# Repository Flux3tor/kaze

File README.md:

# kaze.

kaze is a custom 65%-style mechanical keyboard powered by the Raspberry Pi Pico (RP2040). It features a custom-designed PCB, a compact 3D-printed case, and RMK firmware.

---

## Why did I make it?

I wanted to build my own keyboard instead of buying one off the shelf. kaze is my take on a compact, silent mechanical keyboard, designed around the layout and features I actually want.

---

## Project Images

### Schematic

### PCB

### PCB Render

### Case Render

---

Features:
- 68-key custom layout
- Raspberry Pi Pico (RP2040) controller
- Custom KiCad PCB and schematic
- Individual diodes for the switch matrix
- Custom case design
- RMK firmware written in Rust
- Base layer and Fn layer
- Dedicated arrow keys
- Brightness and volume controls in the keymap

---

## Firmware

Kaze. uses [RMK](https://github.com/HaoboGu/rmk), a Rust-based keyboard firmware.

The firmware configuration is in [`Firmware/keyboard.toml`](Firmware/keyboard.toml), and the configurator definition is in [`Firmware/vial.json`](Firmware/vial.json).

---

## BOM

| Name | Purpose | Quantity | Unit Cost (USD) | Total Cost (USD) | Distributor |
|---|---|---:|---:|---:|---|
| [Akko V3 Fairy Pro Switches (Pack of 45)](https://stackskb.com/store/akko-fairy-pro-switch-pack-of-45/) | Mechanical switches | 2 | $16.00 | $32.00 | StacksKB |
| [Lakes Mountains Premium Cherry PBT Extended Keycaps](https://curiositycaps.in/products/lakes-mountains-premium-cherry-pbt-extended-keycaps) | Keycaps | 1 | $29.00 | $29.00 | Curiosity Caps |
| [Durock Clear Screw-In Stabilizers V2](https://stackskb.com/store/durock-clear-screw-in-stabilizers-v2/?attribute_combination=4%2B1+Set&attribute_spacebar-size=6.25U) | Stabilizers | 1 | $17.00 | $17.00 | StacksKB |
| [1N4148 Through-Hole Diodes (Pack of 10)](https://stackskb.com/store/1n4148-through-hole-diode/) | Matrix diodes | 7 | $0.20 | $2 | StacksKB |
| [LuatOS USB-C Raspberry Pi Pico Development Board](https://makerbazar.in/products/luatos-usb-c-raspberry-pi-pico-development-board-based-on-rp2040-microcontroller) | Main controller | 1 | $5.00 | $5.00 | MakerBazar |
| [Portronics Type-C to Type-C Cable](https://www.amazon.in/dp/B09Q8XMFHB?ref_=cm_sw_r_cp_ud_dp_9F8YCTNXZB2SQ3WDDXEK_1) | USB connection | 1 | $2.00 | $2.00 | Amazon |
| [PLA Filament](https://india.numakers.com/products/pla-filament) | 3D-printed case | 1 | Already owned | $0.00 | Numakers |
| PCB | Keyboard circuit board | 5 | 25 | 25 | Offline/Local Fabricator |
| M2 Screws | Case mounting | 6 | Already owned | $0.00 | Already owned |
| M2 Brass Inserts | Case mounting inserts | 6 | Already owned | $0.00 | Already owned |

## Total Pricing
The total price comes out to be **₹10,600 ($112), including shipping, and taxes.**

---

## Project Files

- `CAD/` - case and assembly CAD files
- `Firmware/` - firmware configuration and UF2 file
- `Images/` - project renders and schematic/PCB images
- `PCB/` - KiCad schematic, PCB, and production files

---

Made with <3 by [Flux3tor](https://github.com/Flux3tor)

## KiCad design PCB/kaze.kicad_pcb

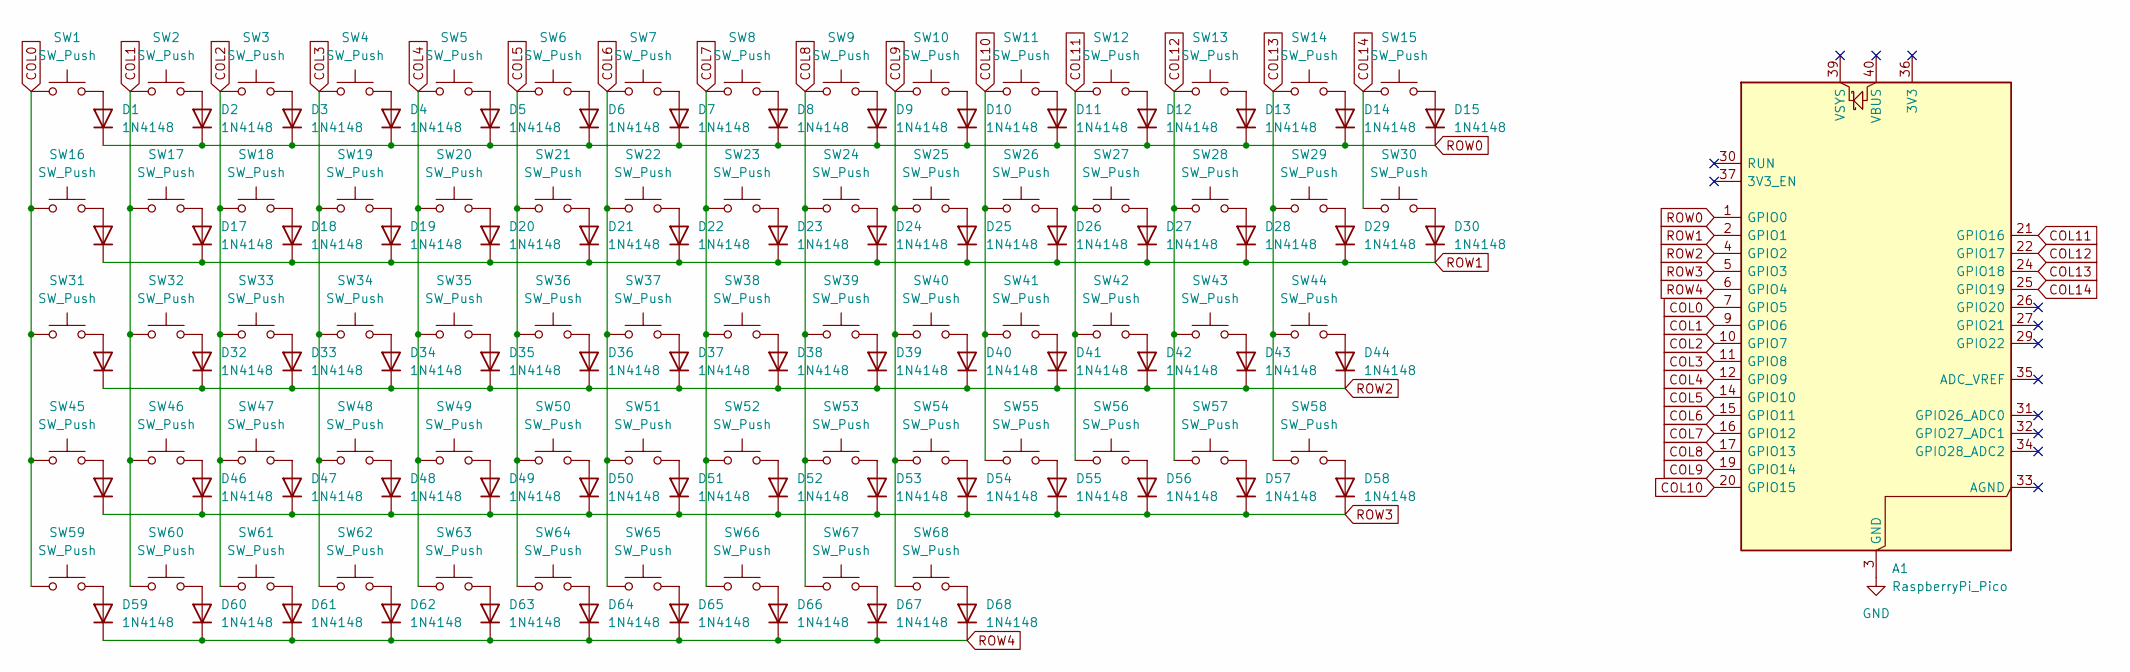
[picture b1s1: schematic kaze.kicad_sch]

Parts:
A1: RaspberryPi_Pico; RaspberryPi_Pico_Common_Unspecified
D1, D2, D3, D4, D5, D6, D7, D8, D9, D10, D11, D12, D13, D14, D15, D16, D17, D18, D19, D20, D21, D22, D23, D24, D25, D26, D27, D28, D29, D30, D31, D32, D33, D34, D35, D36, D37, D38, D39, D40, D41, D42, D43, D44, D45, D46, D47, D48, D49, D50, D51, D52, D53, D54, D55, D56, D57, D58, D59, D60, D61, D62, D63, D64, D65, D66, D67, D68: 1N4148; D_DO-35_SOD27_P7.62mm_Horizontal
SW1, SW2, SW3, SW4, SW5, SW6, SW7, SW8, SW9, SW10, SW11, SW12, SW13, SW15, SW17, SW18, SW19, SW20, SW21, SW22, SW23, SW24, SW25, SW26, SW27, SW28, SW30, SW32, SW33, SW34, SW35, SW36, SW37, SW38, SW39, SW40, SW41, SW42, SW44, SW46, SW47, SW48, SW49, SW50, SW51, SW52, SW53, SW54, SW55, SW57, SW58, SW63, SW64, SW65, SW66, SW67, SW68: SW_Push; SW_Cherry_MX_1.00u_PCB
SW14: SW_Push; SW_Cherry_MX_2.00u_PCB
SW16, SW29: SW_Push; SW_Cherry_MX_1.50u_PCB
SW31, SW56: SW_Push; SW_Cherry_MX_1.75u_PCB
SW43, SW45: SW_Push; SW_Cherry_MX_2.25u_PCB
SW59, SW60, SW61: SW_Push; SW_Cherry_MX_1.25u_PCB
SW62: SW_Push; SW_Cherry_MX_6.25u_PCB

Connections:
COL0: A1.7 (GPIO5), SW1.1, SW16.1, SW31.1, SW45.1, SW59.1
COL1: A1.9 (GPIO6), SW2.1, SW17.1, SW32.1, SW46.1, SW60.1
COL2: A1.10 (GPIO7), SW3.1, SW18.1, SW33.1, SW47.1, SW61.1
COL3: A1.11 (GPIO8), SW4.1, SW19.1, SW34.1, SW48.1, SW62.1
COL4: A1.12 (GPIO9), SW5.1, SW20.1, SW35.1, SW49.1, SW63.1
COL5: A1.14 (GPIO10), SW6.1, SW21.1, SW36.1, SW50.1, SW64.1
COL6: A1.15 (GPIO11), SW7.1, SW22.1, SW37.1, SW51.1, SW65.1
COL7: A1.16 (GPIO12), SW8.1, SW23.1, SW38.1, SW52.1, SW66.1
COL8: A1.17 (GPIO13), SW9.1, SW24.1, SW39.1, SW53.1, SW67.1
COL9: A1.19 (GPIO14), SW10.1, SW25.1, SW40.1, SW54.1, SW68.1
COL10: A1.20 (GPIO15), SW11.1, SW26.1, SW41.1, SW55.1
COL11: A1.21 (GPIO16), SW12.1, SW27.1, SW42.1, SW56.1
COL12: A1.22 (GPIO17), SW13.1, SW28.1, SW43.1, SW57.1
COL13: A1.24 (GPIO18), SW14.1, SW29.1, SW44.1, SW58.1
COL14: A1.25 (GPIO19), SW15.1, SW30.1
GND: A1.3 (GND), A1.8 (GND), A1.13 (GND), A1.18 (GND), A1.23 (GND), A1.28 (GND), A1.38 (GND)
unnamed: D1.2 (A), SW1.2
unnamed: D2.2 (A), SW2.2
unnamed: D3.2 (A), SW3.2
unnamed: D4.2 (A), SW4.2
unnamed: D5.2 (A), SW5.2
unnamed: D6.2 (A), SW6.2
unnamed: D7.2 (A), SW7.2
unnamed: D8.2 (A), SW8.2
unnamed: D9.2 (A), SW9.2
unnamed: D10.2 (A), SW10.2
unnamed: D11.2 (A), SW11.2
unnamed: D12.2 (A), SW12.2
unnamed: D13.2 (A), SW13.2
unnamed: D14.2 (A), SW14.2
unnamed: D15.2 (A), SW15.2
unnamed: D16.2 (A), SW16.2
unnamed: D17.2 (A), SW17.2
unnamed: D18.2 (A), SW18.2
unnamed: D19.2 (A), SW19.2
unnamed: D20.2 (A), SW20.2
unnamed: D21.2 (A), SW21.2
unnamed: D22.2 (A), SW22.2
unnamed: D23.2 (A), SW23.2
unnamed: D24.2 (A), SW24.2
unnamed: D25.2 (A), SW25.2
unnamed: D26.2 (A), SW26.2
unnamed: D27.2 (A), SW27.2
unnamed: D28.2 (A), SW28.2
unnamed: D29.2 (A), SW29.2
unnamed: D30.2 (A), SW30.2
unnamed: D31.2 (A), SW31.2
unnamed: D32.2 (A), SW32.2
unnamed: D33.2 (A), SW33.2
unnamed: D34.2 (A), SW34.2
unnamed: D35.2 (A), SW35.2
unnamed: D36.2 (A), SW36.2
unnamed: D37.2 (A), SW37.2
unnamed: D38.2 (A), SW38.2
unnamed: D39.2 (A), SW39.2
unnamed: D40.2 (A), SW40.2
unnamed: D41.2 (A), SW41.2
unnamed: D42.2 (A), SW42.2
unnamed: D43.2 (A), SW43.2
unnamed: D44.2 (A), SW44.2
unnamed: D45.2 (A), SW45.2
unnamed: D46.2 (A), SW46.2
unnamed: D47.2 (A), SW47.2
unnamed: D48.2 (A), SW48.2
unnamed: D49.2 (A), SW49.2
unnamed: D50.2 (A), SW50.2
unnamed: D51.2 (A), SW51.2
unnamed: D52.2 (A), SW52.2
unnamed: D53.2 (A), SW53.2
unnamed: D54.2 (A), SW54.2
unnamed: D55.2 (A), SW55.2
unnamed: D56.2 (A), SW56.2
unnamed: D57.2 (A), SW57.2
unnamed: D58.2 (A), SW58.2
unnamed: D59.2 (A), SW59.2
unnamed: D60.2 (A), SW60.2
unnamed: D61.2 (A), SW61.2
unnamed: D62.2 (A), SW62.2
unnamed: D63.2 (A), SW63.2
unnamed: D64.2 (A), SW64.2
unnamed: D65.2 (A), SW65.2
unnamed: D66.2 (A), SW66.2
unnamed: D67.2 (A), SW67.2
unnamed: D68.2 (A), SW68.2
ROW0: A1.1 (GPIO0), D1.1 (K), D2.1 (K), D3.1 (K), D4.1 (K), D5.1 (K), D6.1 (K), D7.1 (K), D8.1 (K), D9.1 (K), D10.1 (K), D11.1 (K), D12.1 (K), D13.1 (K), D14.1 (K), D15.1 (K)
ROW1: A1.2 (GPIO1), D16.1 (K), D17.1 (K), D18.1 (K), D19.1 (K), D20.1 (K), D21.1 (K), D22.1 (K), D23.1 (K), D24.1 (K), D25.1 (K), D26.1 (K), D27.1 (K), D28.1 (K), D29.1 (K), D30.1 (K)
ROW2: A1.4 (GPIO2), D31.1 (K), D32.1 (K), D33.1 (K), D34.1 (K), D35.1 (K), D36.1 (K), D37.1 (K), D38.1 (K), D39.1 (K), D40.1 (K), D41.1 (K), D42.1 (K), D43.1 (K), D44.1 (K)
ROW3: A1.5 (GPIO3), D45.1 (K), D46.1 (K), D47.1 (K), D48.1 (K), D49.1 (K), D50.1 (K), D51.1 (K), D52.1 (K), D53.1 (K), D54.1 (K), D55.1 (K), D56.1 (K), D57.1 (K), D58.1 (K)
ROW4: A1.6 (GPIO4), D59.1 (K), D60.1 (K), D61.1 (K), D62.1 (K), D63.1 (K), D64.1 (K), D65.1 (K), D66.1 (K), D67.1 (K), D68.1 (K)

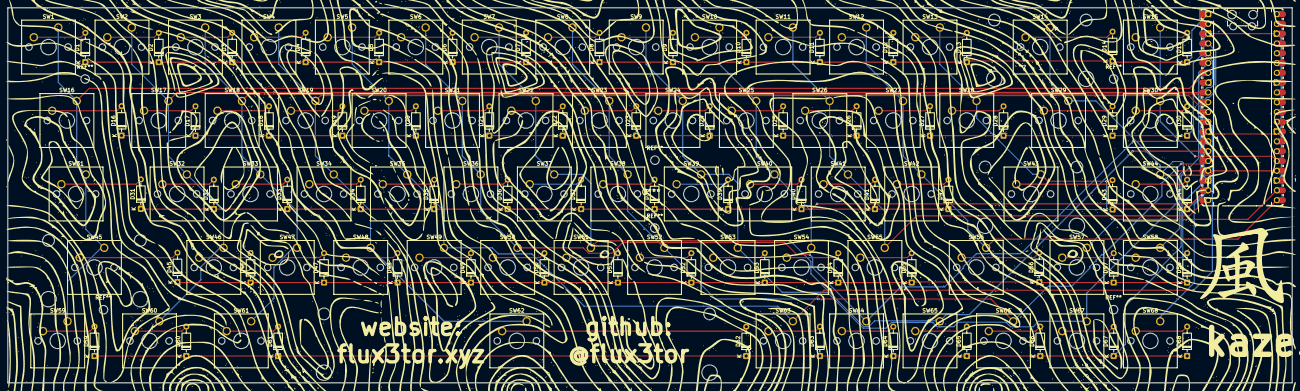
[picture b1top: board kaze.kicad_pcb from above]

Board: 2 copper layers, 333.1 x 97.3 mm, 137 parts (0 on the bottom side), 89 nets.

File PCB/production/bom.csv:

Designator,Footprint,Quantity,Value,LCSC Part #
A1,RaspberryPi_Pico_Common_Unspecified,1,RaspberryPi_Pico,
"D1, D10, D11, D12, D13, D14, D15, D16, D17, D18, D19, D2, D20, D21, D22, D23, D24, D25, D26, D27, D28, D29, D3, D30, D31, D32, D33, D34, D35, D36, D37, D38, D39, D4, D40, D41, D42, D43, D44, D45, D46, D47, D48, D49, D5, D50, D51, D52, D53, D54, D55, D56, D57, D58, D59, D6, D60, D61, D62, D63, D64, D65, D66, D67, D68, D7, D8, D9",D_DO-35_SOD27_P7.62mm_Horizontal,68,1N4148,
"SW1, SW10, SW11, SW12, SW13, SW15, SW17, SW18, SW19, SW2, SW20, SW21, SW22, SW23, SW24, SW25, SW26, SW27, SW28, SW3, SW30, SW32, SW33, SW34, SW35, SW36, SW37, SW38, SW39, SW4, SW40, SW41, SW42, SW44, SW46, SW47, SW48, SW49, SW5, SW50, SW51, SW52, SW53, SW54, SW55, SW57, SW58, SW6, SW63, SW64, SW65, SW66, SW67, SW68, SW7, SW8, SW9",SW_Cherry_MX_1.00u_PCB,57,SW_Push,
SW14,SW_Cherry_MX_2.00u_PCB,1,SW_Push,
"SW16, SW29",SW_Cherry_MX_1.50u_PCB,2,SW_Push,
"SW31, SW56",SW_Cherry_MX_1.75u_PCB,2,SW_Push,
"SW43, SW45",SW_Cherry_MX_2.25u_PCB,2,SW_Push,
"SW59, SW60, SW61",SW_Cherry_MX_1.25u_PCB,3,SW_Push,
SW62,SW_Cherry_MX_6.25u_PCB,1,SW_Push,
